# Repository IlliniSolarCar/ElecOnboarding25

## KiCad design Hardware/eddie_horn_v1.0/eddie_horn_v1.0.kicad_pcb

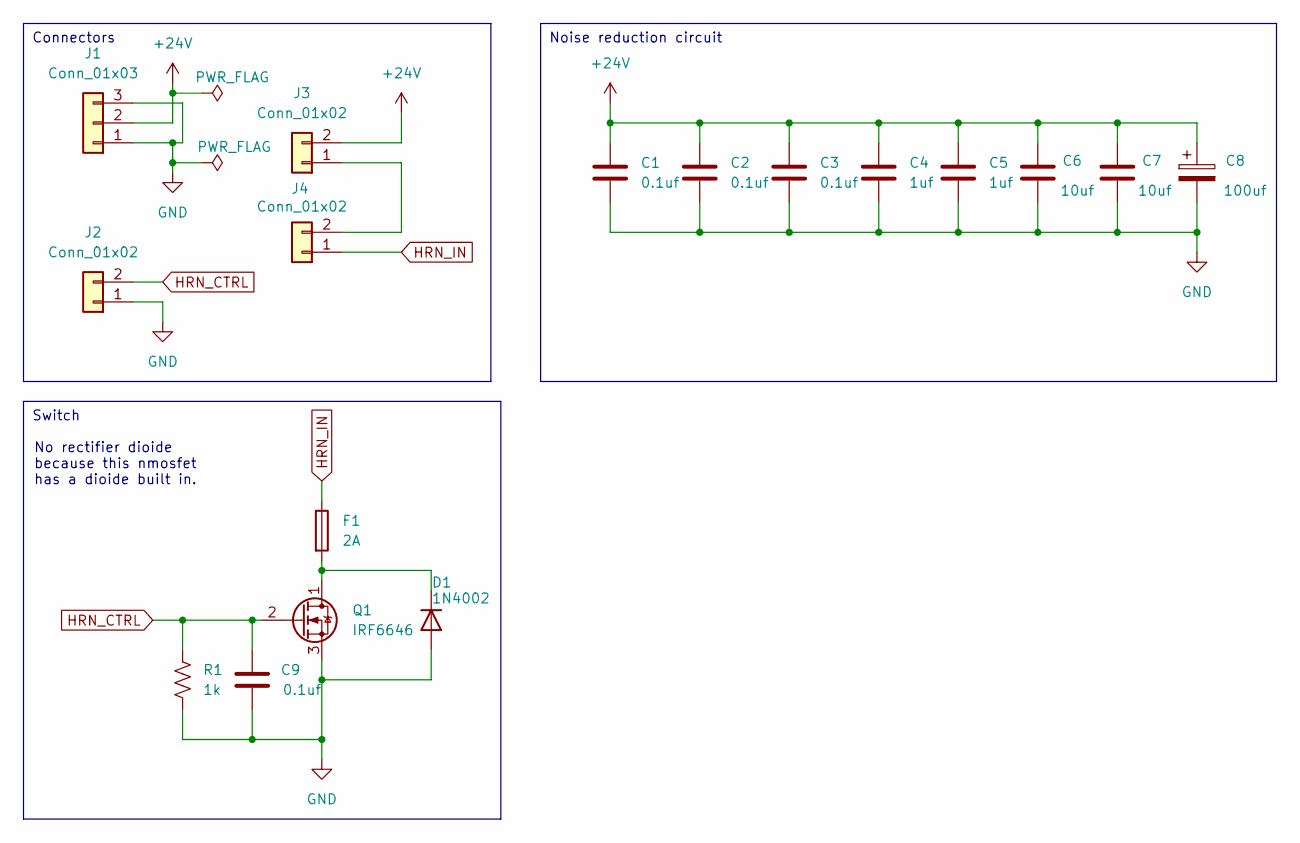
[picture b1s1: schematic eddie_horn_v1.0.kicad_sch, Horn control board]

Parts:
C1, C2, C3, C9: 0.1uf; C_0603_1608Metric_Pad1.08x0.95mm_HandSolder
C4, C5: 1uf; C_0603_1608Metric_Pad1.08x0.95mm_HandSolder
C6, C7: 10uf; C_0603_1608Metric_Pad1.08x0.95mm_HandSolder
C8: 100uf; CP_Radial_D10.0mm_P5.00mm
D1: 1N4002; D_DO-41_SOD81_P10.16mm_Horizontal
F1: 2A; Fuse_0603_1608Metric_Pad1.05x0.95mm_HandSolder
J1: Conn_01x03; Molex_Micro-Fit_3.0_43650-0300_1x03_P3.00mm_Horizontal
J2, J3, J4: Conn_01x02; Molex_Micro-Fit_3.0_43650-0200_1x02_P3.00mm_Horizontal
Q1: IRF6646; DirectFET_MN
R1: 1k; R_0603_1608Metric_Pad0.98x0.95mm_HandSolder

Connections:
+24V: C1.1, C2.1, C3.1, C4.1, C5.1, C6.1, C7.1, C8.1, J1.2, J3.2; also elsewhere on the board
GND: C1.2, C2.2, C3.2, C4.2, C5.2, C6.2, C7.2, C8.2, C9.2, D1.2 (A), J1.1, J1.3, J2.1, Q1.3 (S), R1.2
HRN_CTRL: C9.1, J2.2, Q1.2 (G), R1.1
HRN_IN: F1.1, J4.1; also elsewhere on the board
unnamed: J3.1, J4.2
unnamed: D1.1 (K), F1.2, Q1.1 (D)

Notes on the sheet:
Connectors
Noise reduction circuit
Switch
No rectifier dioide because this nmosfet has a dioide built in.

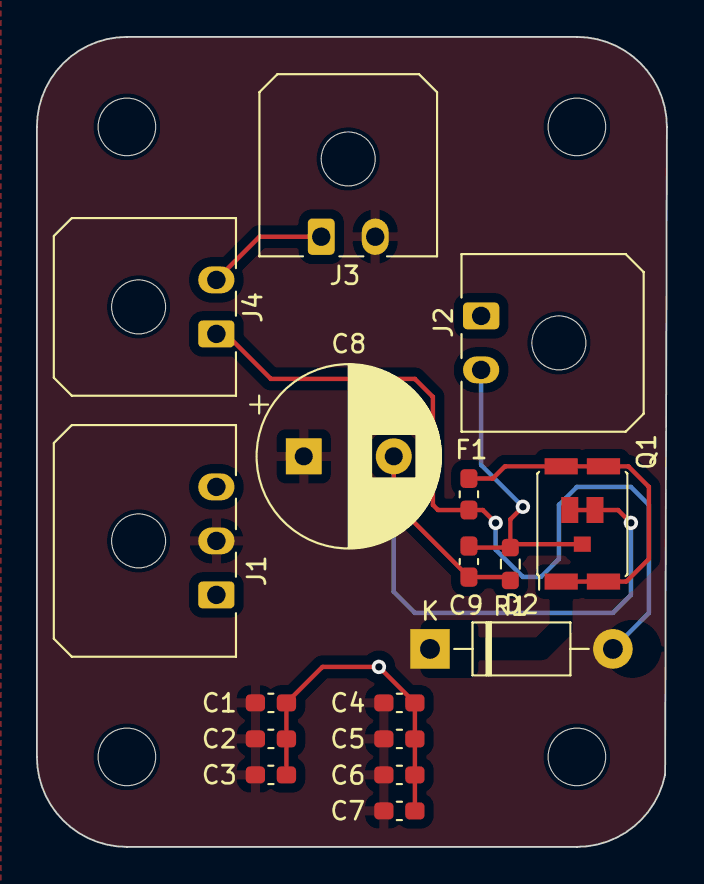
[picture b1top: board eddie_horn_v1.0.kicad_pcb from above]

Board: 2 copper layers, 35.0 x 45.0 mm, 17 parts (0 on the bottom side), 6 nets.

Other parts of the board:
D2: 1N4002; D_DO-41_SOD81_P10.16mm_Horizontal

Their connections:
+24V: D2.1 (K); also elsewhere on the board
HRN_IN: D2.2 (A); also elsewhere on the board

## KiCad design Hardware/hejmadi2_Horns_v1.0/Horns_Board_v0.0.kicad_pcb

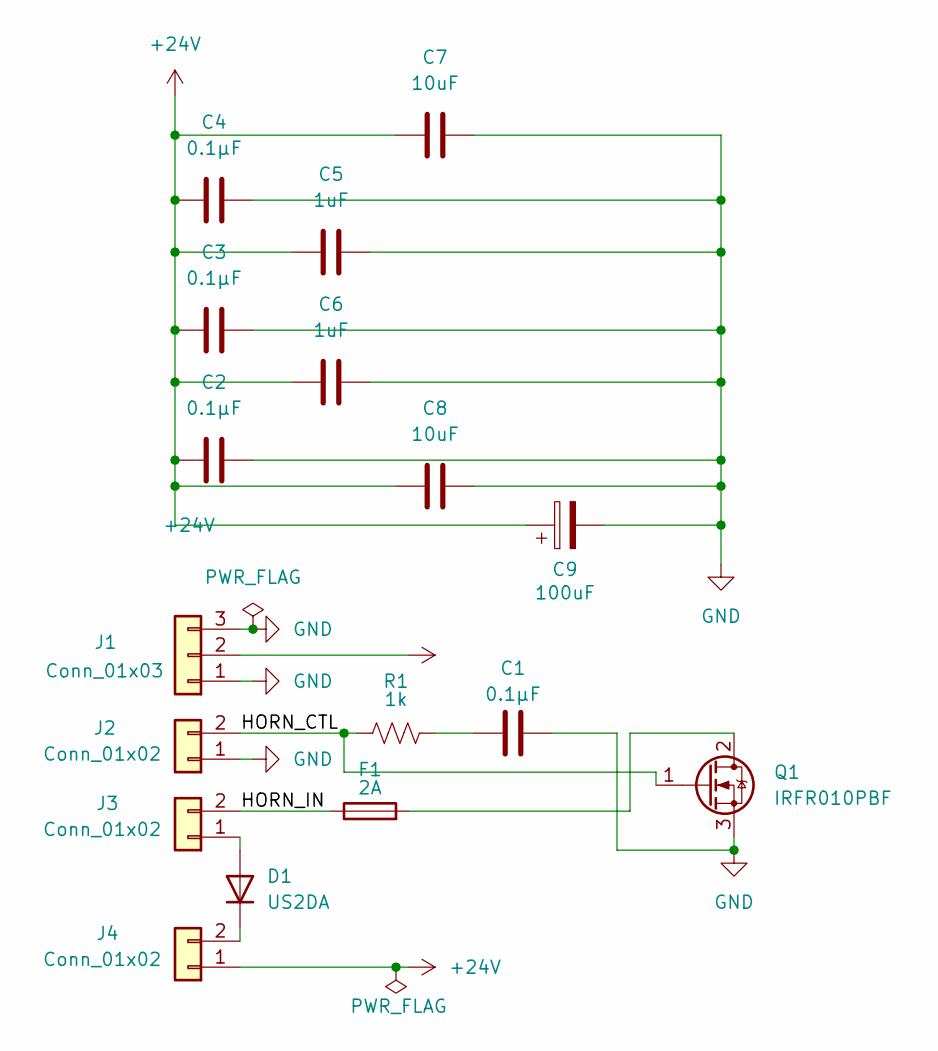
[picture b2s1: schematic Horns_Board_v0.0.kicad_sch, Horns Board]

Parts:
C1, C2, C3, C4: 0.1µF; C_0603_1608Metric_Pad1.08x0.95mm_HandSolder
C5, C6: 1uF; C_0603_1608Metric_Pad1.08x0.95mm_HandSolder
C7, C8: 10uF; C_0603_1608Metric_Pad1.08x0.95mm_HandSolder
C9: 100uF; C_0603_1608Metric_Pad1.08x0.95mm_HandSolder
D1: US2DA; D_SMA
F1: 2A; Fuse_0603_1608Metric_Pad1.05x0.95mm_HandSolder
J1: Conn_01x03; Molex_Micro-Fit_3.0_43650-0300_1x03_P3.00mm_Horizontal
J2, J3, J4: Conn_01x02; Molex_Micro-Fit_3.0_43650-0200_1x02_P3.00mm_Horizontal
Q1: IRFR010PBF; Fairchild_DualPower33-6_3x3mm
R1: 1k; R_0603_1608Metric_Pad0.98x0.95mm_HandSolder

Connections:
+24V: C2.1, C3.1, C4.1, C5.1, C6.1, C7.1, C8.1, C9.1, J1.2, J4.1
/HORN_CTL: J2.2, Q1.1 (G), R1.1
/HORN_IN: F1.1, J3.2
GND: C1.2, C2.2, C3.2, C4.2, C5.2, C6.2, C7.2, C8.2, C9.2, J1.1, J1.3, J2.1, Q1.3 (S)
unnamed: C1.1, R1.2
unnamed: D1.2 (A), J3.1
unnamed: D1.1 (K), J4.2
unnamed: F1.2, Q1.2 (D)

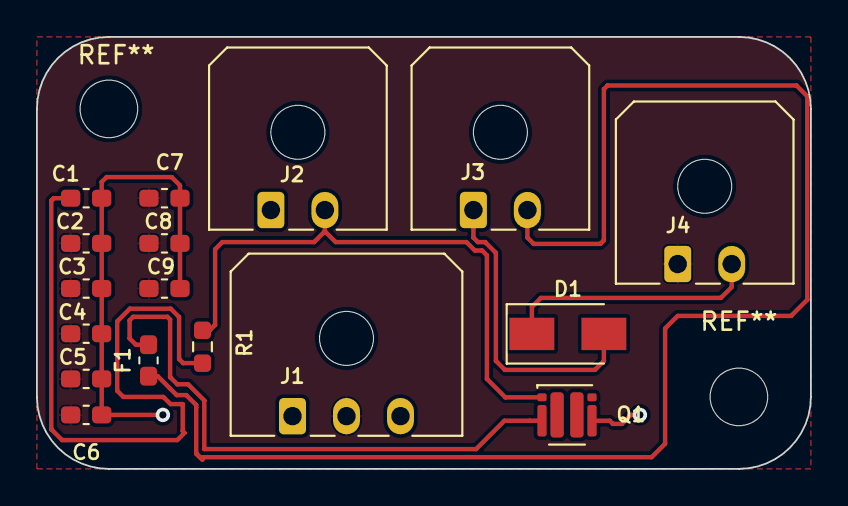
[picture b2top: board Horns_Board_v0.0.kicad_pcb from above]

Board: 2 copper layers, 43.0 x 24.0 mm, 17 parts (0 on the bottom side), 8 nets.

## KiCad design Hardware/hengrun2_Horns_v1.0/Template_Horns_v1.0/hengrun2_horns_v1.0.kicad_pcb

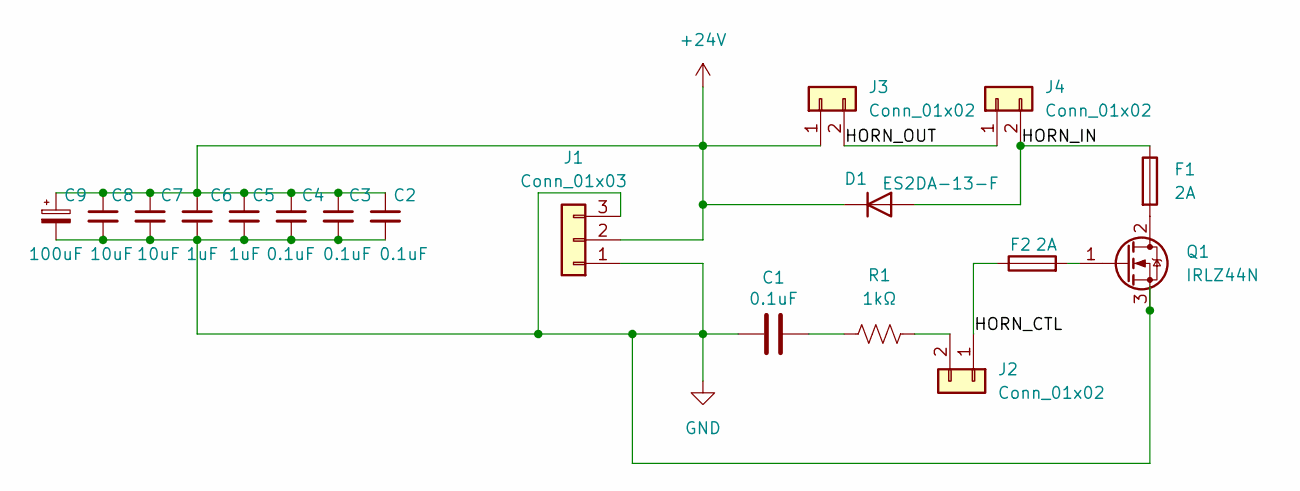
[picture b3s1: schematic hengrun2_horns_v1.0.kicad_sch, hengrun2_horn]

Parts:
C1, C2, C3, C4: 0.1uF; C_0603_1608Metric
C5, C6: 1uF; C_0603_1608Metric
C7, C8: 10uF; C_0603_1608Metric
C9: 100uF; CP_Radial_D5.0mm_P2.50mm
D1: ES2DA-13-F; D_SMA
F1, F2: 2A; Fuse_1206_3216Metric
J1: Conn_01x03; Molex_KK-254_AE-6410-03A_1x03_P2.54mm_Vertical
J2, J3, J4: Conn_01x02; Molex_KK-254_AE-6410-02A_1x02_P2.54mm_Vertical
Q1: IRLZ44N; TO-220-3_Vertical
R1: 1kΩ; R_0603_1608Metric_Pad0.98x0.95mm_HandSolder

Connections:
+24V: C2.1, C3.1, C4.1, C5.1, C6.1, C7.1, C8.1, C9.1, D1.1 (K), J1.2, J3.1
/HORN_CTL: F2.1, J2.1
/HORN_IN: D1.2 (A), F1.1, J4.2
/HORN_OUT: J3.2, J4.1
GND: C1.1, C2.2, C3.2, C4.2, C5.2, C6.2, C7.2, C8.2, C9.2, J1.1, J1.3, Q1.3 (S)
unnamed: C1.2, R1.1
unnamed: J2.2, R1.2
unnamed: F1.2, Q1.2 (D)
unnamed: F2.2, Q1.1 (G)

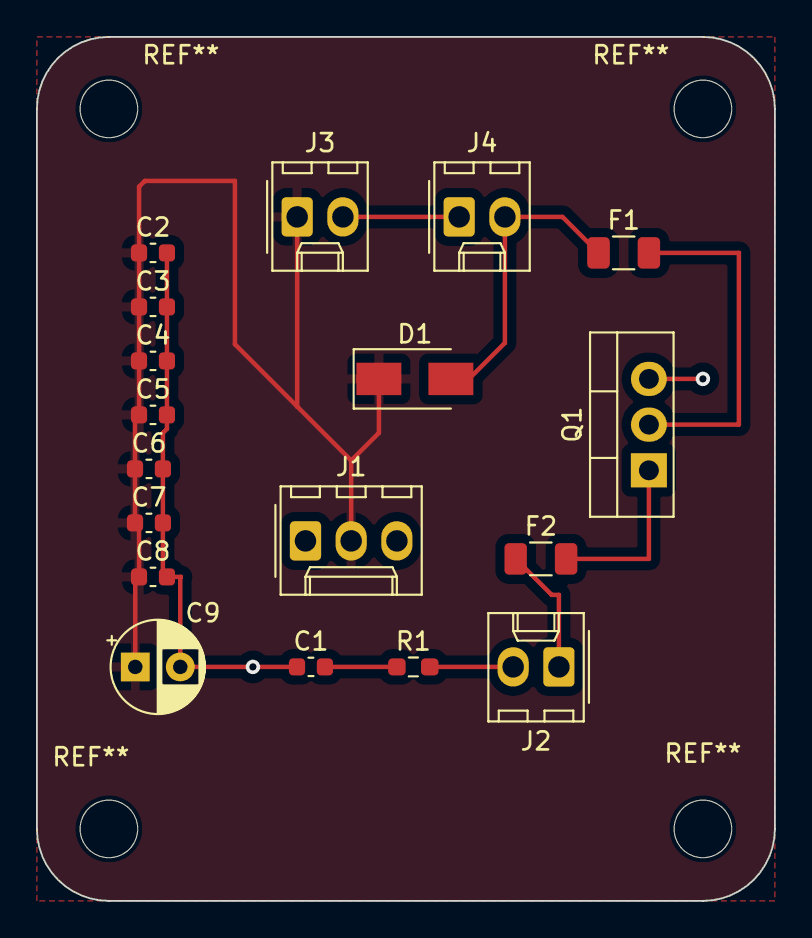
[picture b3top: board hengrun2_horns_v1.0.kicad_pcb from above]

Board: 2 copper layers, 41.0 x 48.0 mm, 18 parts (0 on the bottom side), 9 nets.

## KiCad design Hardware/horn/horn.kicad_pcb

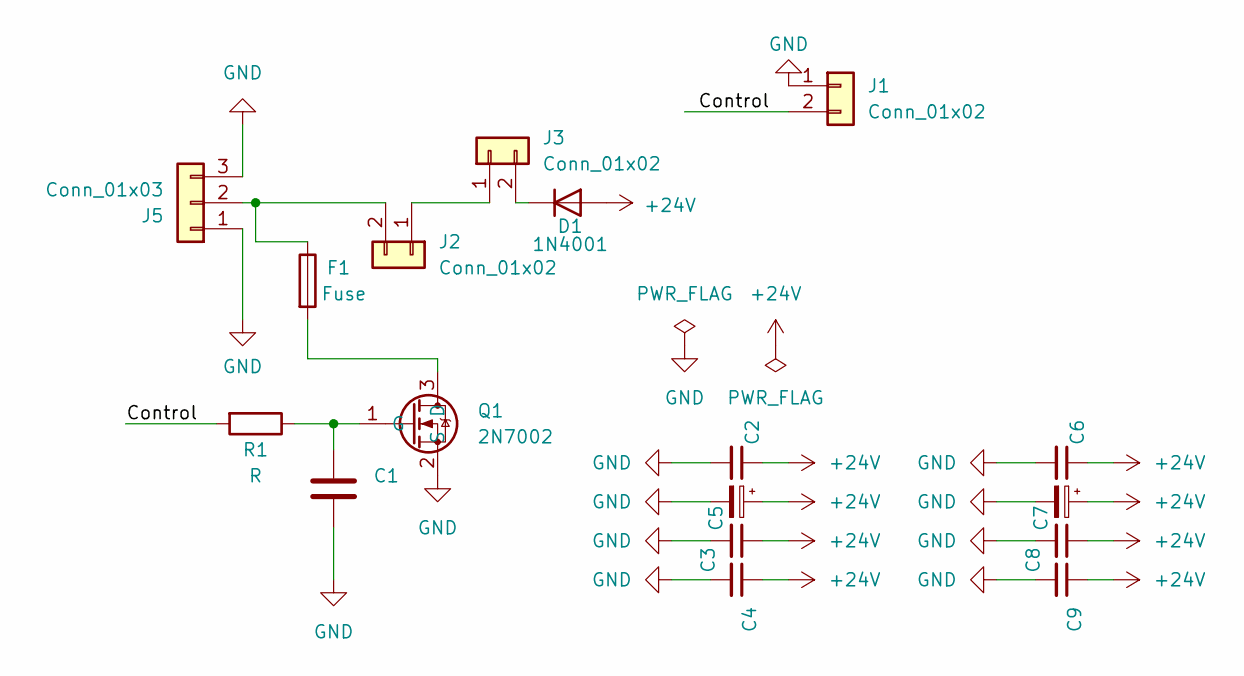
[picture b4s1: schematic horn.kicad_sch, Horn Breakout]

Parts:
C1: C; C_0201_0603Metric
C2, C3, C4, C6, C8, C9: C_Small; C_0201_0603Metric
C5, C7: C_Polarized_Small; CP_Elec_3x5.3
D1: 1N4001; D_DO-41_SOD81_P10.16mm_Horizontal
F1: Fuse; Fuse_0402_1005Metric
J1, J2, J3: Conn_01x02; Molex_KK-254_AE-6410-02A_1x02_P2.54mm_Vertical
J5: Conn_01x03; Molex_KK-254_AE-6410-03A_1x03_P2.54mm_Vertical
Q1: 2N7002; SOT-23
R1: R; R_0603_1608Metric_Pad0.98x0.95mm_HandSolder

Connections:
+24V: C2.1, C3.1, C4.1, C5.1, C6.1, C7.1, C8.1, C9.1, D1.2 (A)
/Control: J1.2, R1.2
GND: C1.2, C2.2, C3.2, C4.2, C5.2, C6.2, C7.2, C8.2, C9.2, J1.1, J5.1, J5.3, Q1.2 (S)
unnamed: D1.1 (K), J3.2
unnamed: J2.1, J3.1
unnamed: F1.1, J2.2, J5.2
unnamed: F1.2, Q1.3 (D)
unnamed: C1.1, Q1.1 (G), R1.1

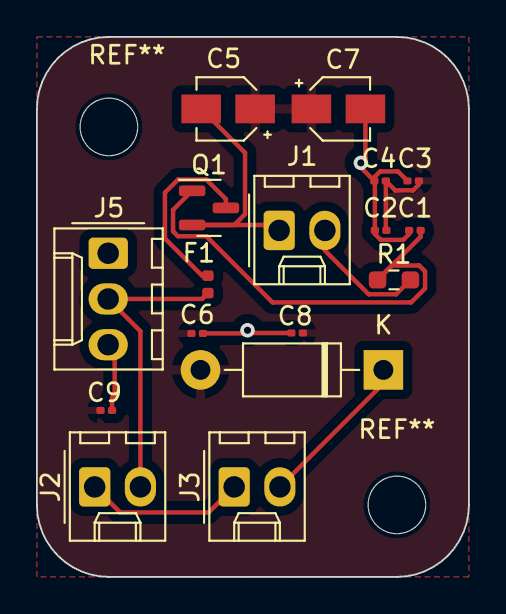
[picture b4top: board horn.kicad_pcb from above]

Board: 2 copper layers, 24.0 x 30.0 mm, 17 parts (0 on the bottom side), 8 nets.

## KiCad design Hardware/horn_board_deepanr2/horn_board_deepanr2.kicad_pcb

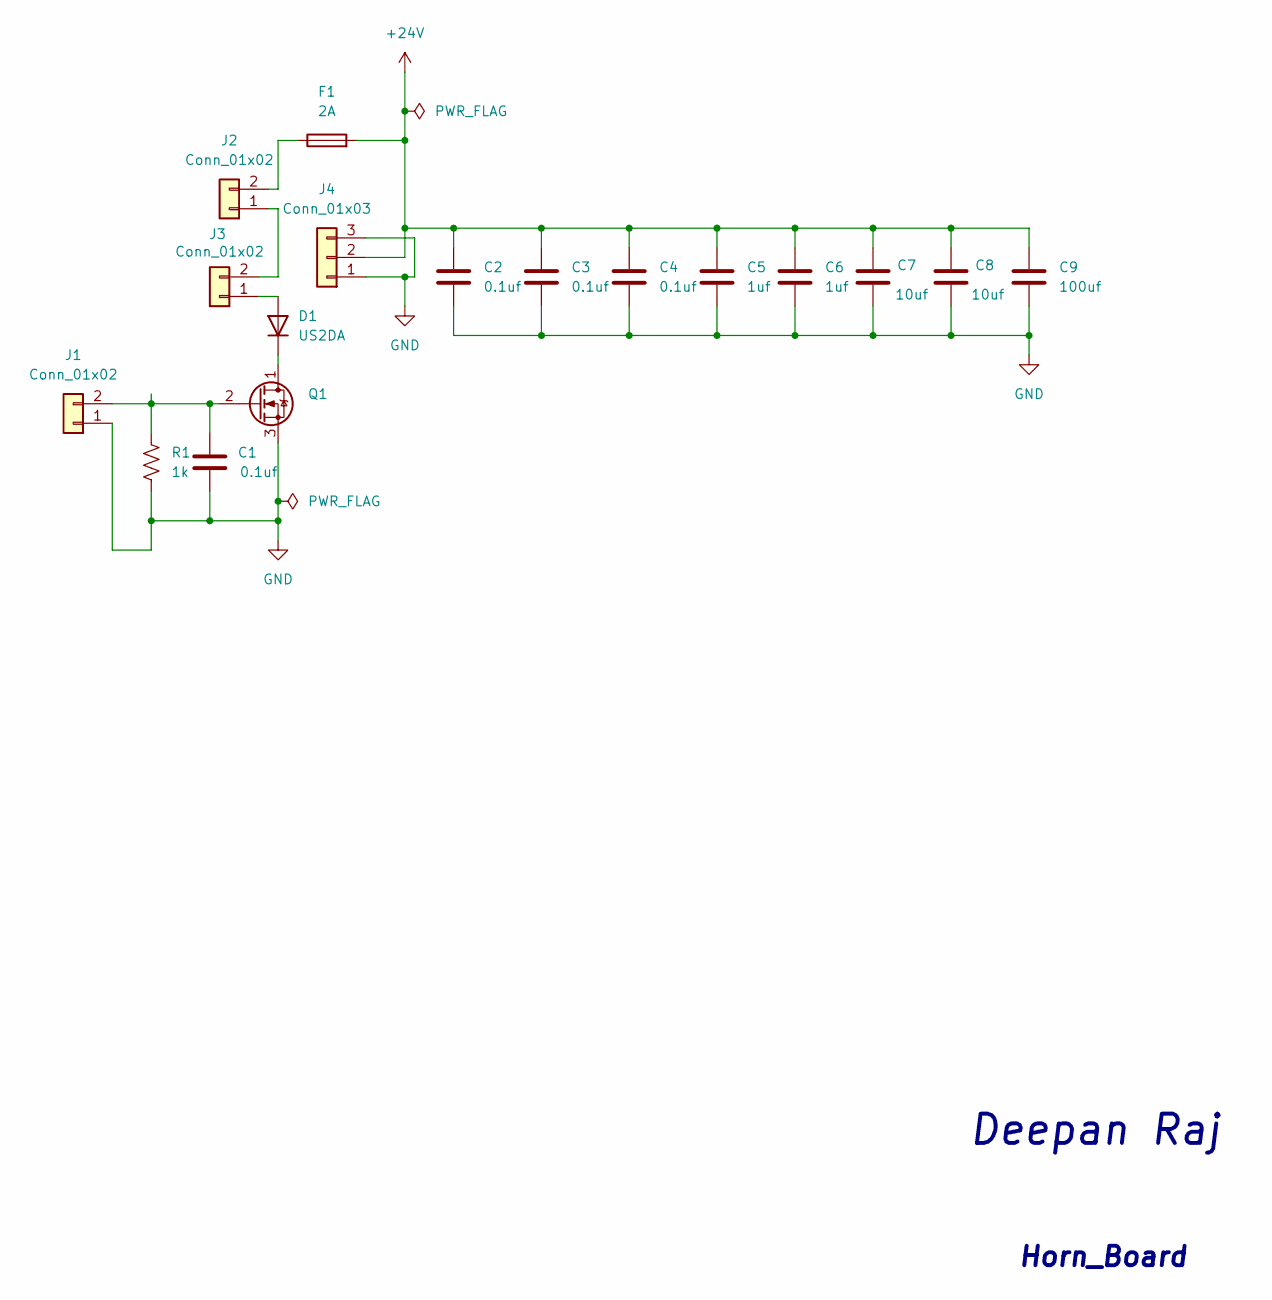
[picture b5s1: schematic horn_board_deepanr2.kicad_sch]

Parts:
C1, C2, C3, C4: 0.1uf; C_0603_1608Metric_Pad1.08x0.95mm_HandSolder
C5, C6: 1uf; C_0603_1608Metric_Pad1.08x0.95mm_HandSolder
C7, C8: 10uf; C_0603_1608Metric_Pad1.08x0.95mm_HandSolder
C9: 100uf
D1: US2DA; D_SMA
F1: 2A; Fuse_0603_1608Metric_Pad1.05x0.95mm_HandSolder
J1, J2, J3: Conn_01x02; Molex_KK-254_AE-6410-02A_1x02_P2.54mm_Vertical
J4: Conn_01x03; Molex_KK-254_AE-6410-03A_1x03_P2.54mm_Vertical
Q1: IRF6646; DirectFET_MN
R1: 1k; R_0603_1608Metric_Pad0.98x0.95mm_HandSolder

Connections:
+24V: C2.1, C3.1, C4.1, C5.1, C6.1, C7.1, C8.1, C9.1, F1.2, J4.2
GND: C1.2, C2.2, C3.2, C4.2, C5.2, C6.2, C7.2, C8.2, C9.2, J1.1, J4.1, J4.3, Q1.3 (S), R1.2
unnamed: D1.2 (A), J3.1
unnamed: D1.1 (K), Q1.1 (D)
unnamed: C1.1, J1.2, Q1.2 (G), R1.1
unnamed: J2.1, J3.2
unnamed: F1.1, J2.2

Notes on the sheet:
Horn_Board
Deepan Raj

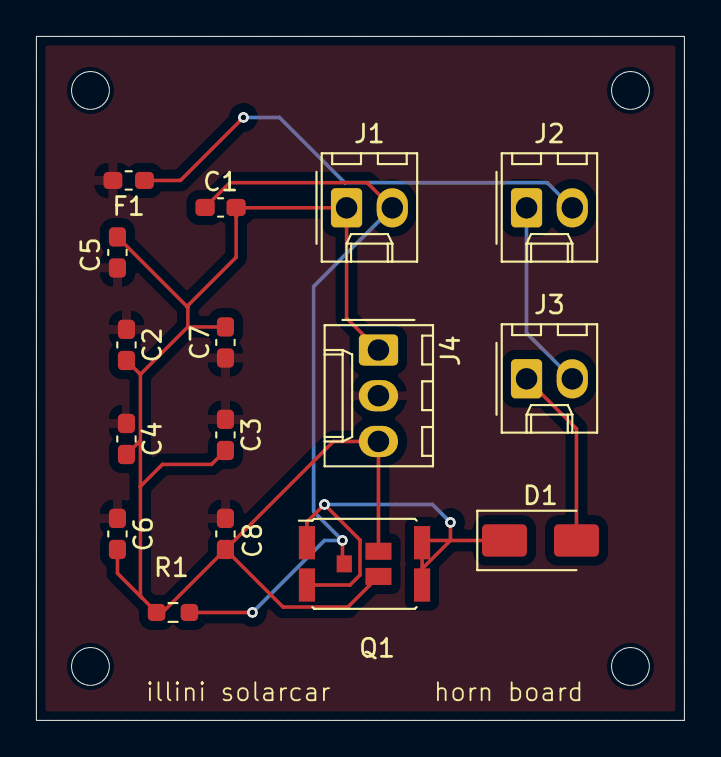
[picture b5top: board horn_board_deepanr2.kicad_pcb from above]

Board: 2 copper layers, 36.0 x 38.0 mm, 16 parts (0 on the bottom side), 7 nets.

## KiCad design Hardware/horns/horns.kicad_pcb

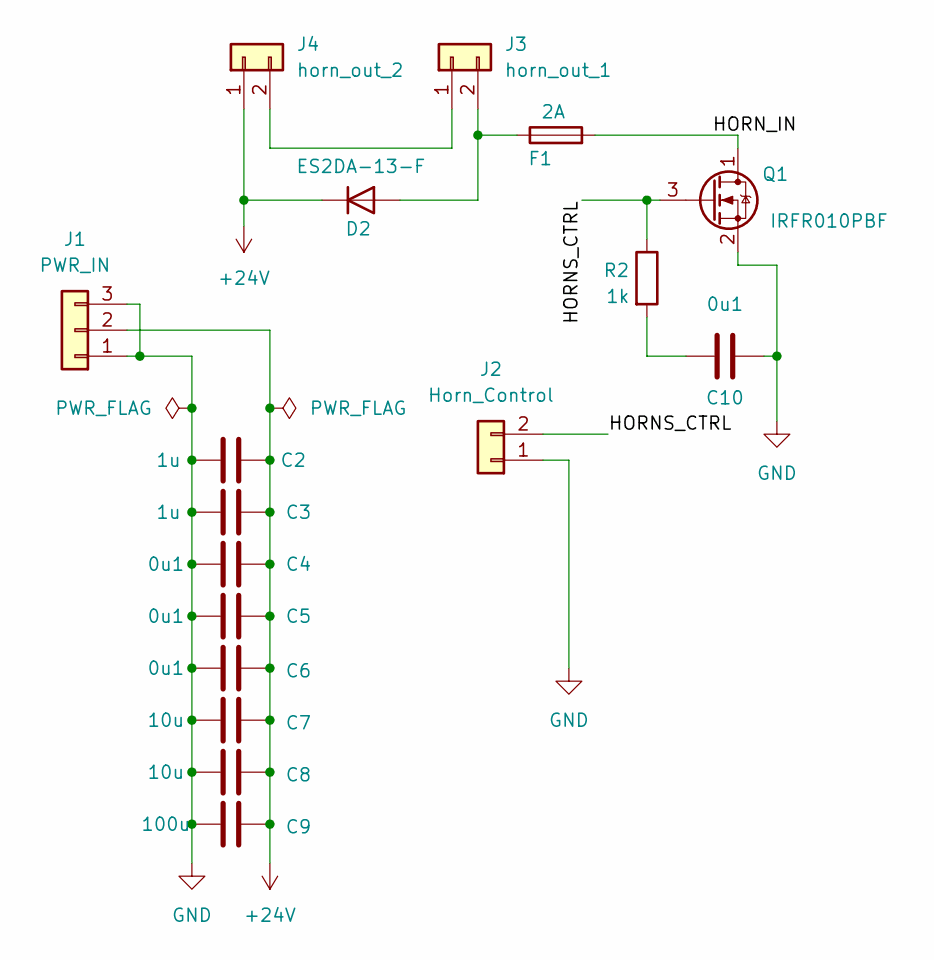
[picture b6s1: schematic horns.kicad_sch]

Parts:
C2, C3: 1u; C_0805_2012Metric
C4, C5, C6, C10: 0u1; C_0805_2012Metric
C7, C8: 10u; C_0805_2012Metric
C9: 100u; CP_Oval_L16.0mm_W8.0mm_P11.5mm
D2: ES2DA-13-F; D_SMA
F1: 2A; Fuse_Littelfuse_1206
J1: PWR_IN; Molex_KK-254_1x03_P2.54mm_Horizontal
J2: Horn_Control; Molex_KK-254_1x02_P2.54mm_Horizontal
J3: horn_out_1; Molex_KK-254_1x02_P2.54mm_Horizontal
J4: horn_out_2; Molex_KK-254_1x02_P2.54mm_Horizontal
Q1: IRFR010PBF; TO-252-2
R2: 1k; R_0603_1608Metric_Pad0.98x0.95mm_HandSolder

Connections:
+24V: C2.2, C3.2, C4.2, C5.2, C6.2, C7.2, C8.2, C9.2, D2.1 (K), J1.2, J4.1; also elsewhere on the board
/HORNS_CTRL: J2.2, Q1.3 (G), R2.1
/HORN_IN: F1.2, Q1.1 (D)
GND: C2.1, C3.1, C4.1, C5.1, C6.1, C7.1, C8.1, C9.1, C10.1, J1.1, J1.3, J2.1, Q1.2 (S); also elsewhere on the board
unnamed: C10.2, R2.2
unnamed: D2.2 (A), F1.1, J3.2
unnamed: J3.1, J4.2

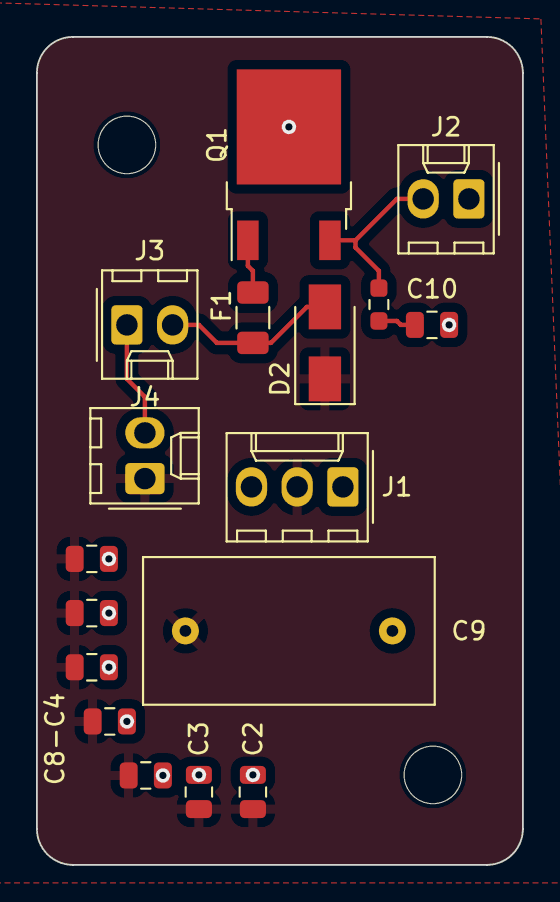
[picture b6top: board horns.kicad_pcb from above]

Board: 2 copper layers, 27.0 x 46.0 mm, 17 parts (0 on the bottom side), 7 nets.

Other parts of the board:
C8-C4: 10u; C_0805_2012Metric

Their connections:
+24V: C8-C4.2; also elsewhere on the board
GND: C8-C4.1; also elsewhere on the board

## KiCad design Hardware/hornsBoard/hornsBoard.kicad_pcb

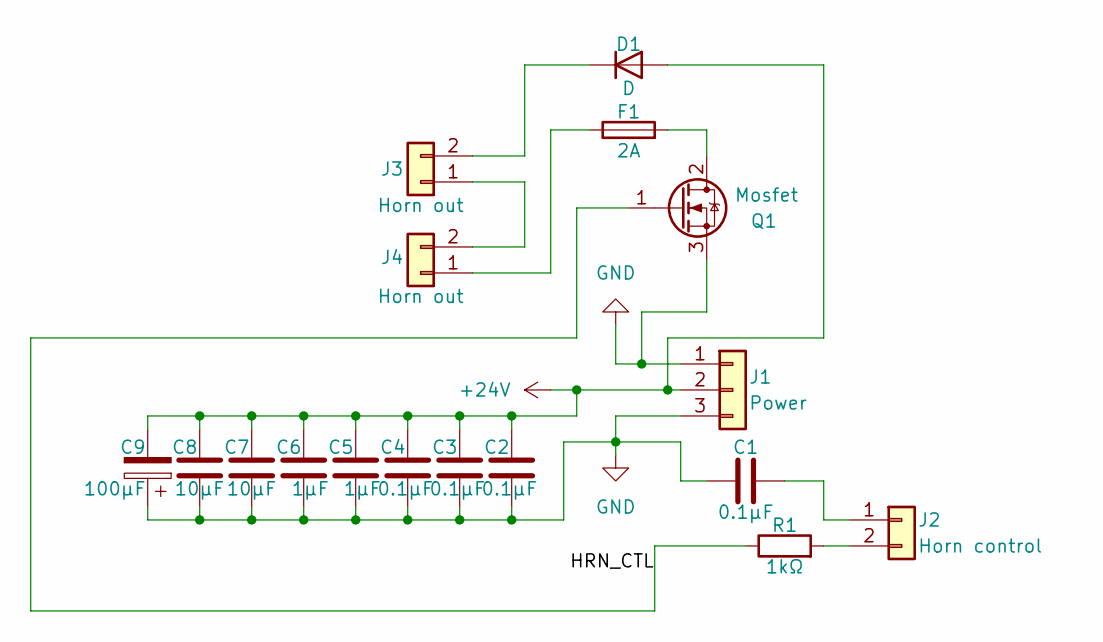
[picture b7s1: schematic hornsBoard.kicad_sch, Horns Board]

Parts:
C1, C2, C3, C4: 0.1µF; C_0603_1608Metric
C5, C6: 1µF; C_0805_2012Metric
C7, C8: 10µF; C_1206_3216Metric
C9: 100µF; C_1210_3225Metric
D1: D; D_SMA
F1: 2A; Fuse_1206_3216Metric
J1: Power; Molex_Micro-Fit_3.0_43650-0300_1x03_P3.00mm_Horizontal
J2: Horn control; Molex_Micro-Fit_3.0_43650-0200_1x02_P3.00mm_Horizontal
J3, J4: Horn out; Molex_Micro-Fit_3.0_43650-0200_1x02_P3.00mm_Horizontal
Q1: Mosfet; TO-252-2
R1: 1kΩ; R_0805_2012Metric

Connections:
+24V: C2.1, C3.1, C4.1, C5.1, C6.1, C7.1, C8.1, C9.2, D1.2 (A), J1.2
/HRN_CTL: Q1.1 (G), R1.1
GND: C1.1, C2.2, C3.2, C4.2, C5.2, C6.2, C7.2, C8.2, C9.1, J1.1, J1.3, Q1.3 (S)
unnamed: D1.1 (K), J3.2
unnamed: C1.2, J2.1
unnamed: J2.2, R1.2
unnamed: J3.1, J4.2
unnamed: F1.1, J4.1
unnamed: F1.2, Q1.2 (D)

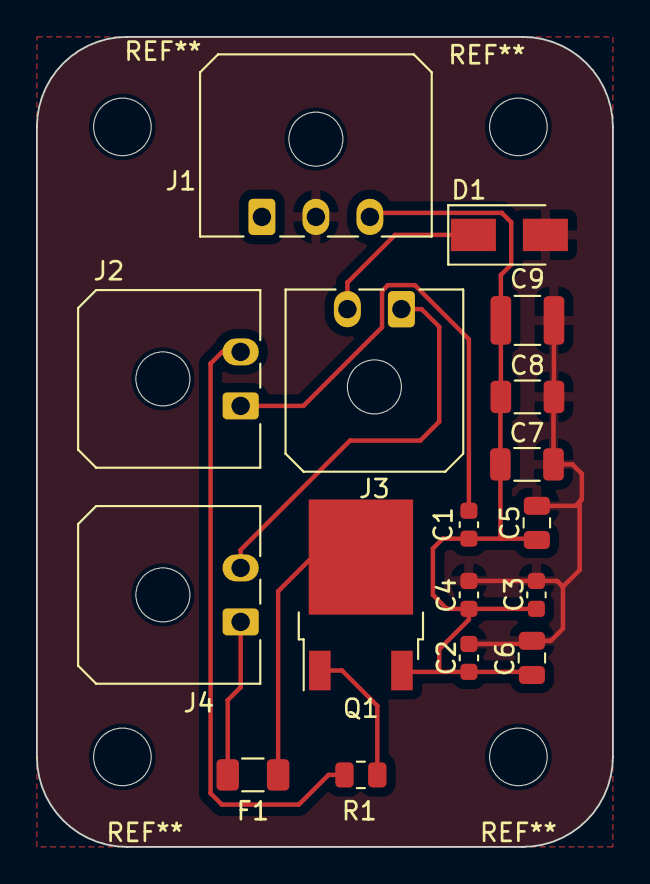
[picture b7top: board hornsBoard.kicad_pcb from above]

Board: 2 copper layers, 32.0 x 45.0 mm, 17 parts (0 on the bottom side), 9 nets.

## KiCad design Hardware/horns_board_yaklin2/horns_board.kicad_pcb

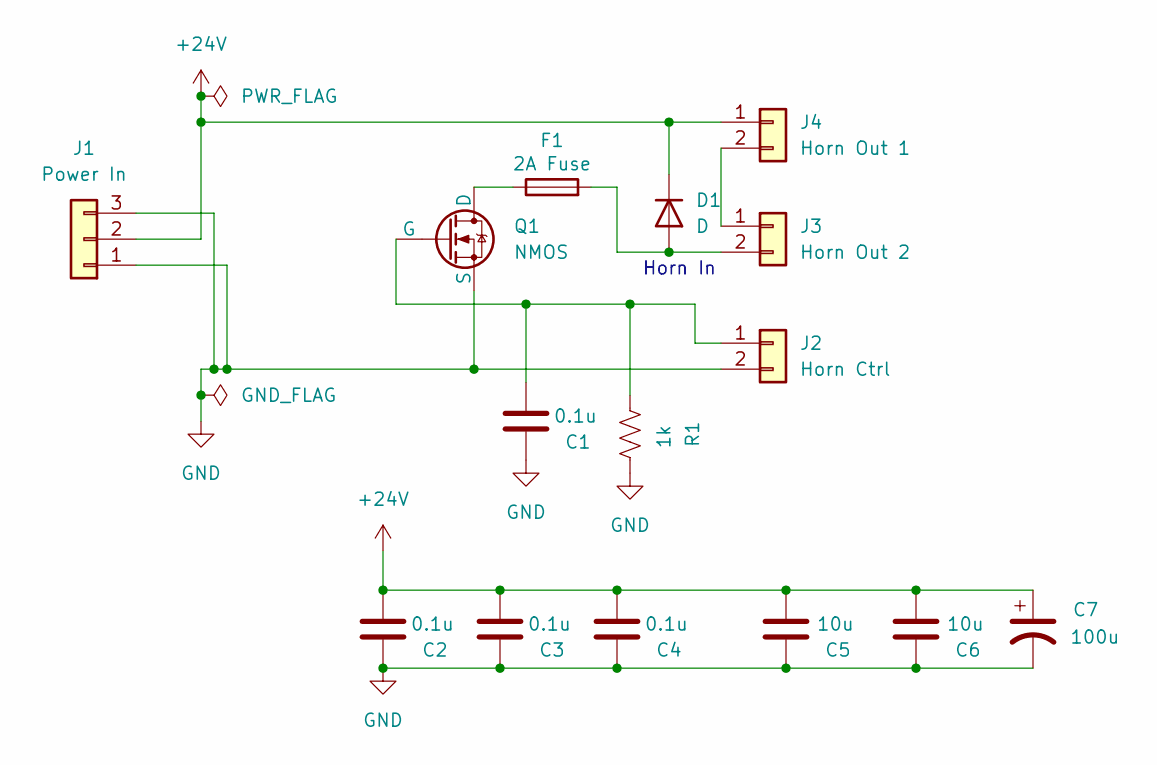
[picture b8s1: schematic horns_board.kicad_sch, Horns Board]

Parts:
C1, C2, C3, C4: 0.1u; C_0603_1608Metric_Pad1.08x0.95mm_HandSolder
C5, C6: 10u; C_0603_1608Metric_Pad1.08x0.95mm_HandSolder
C7: 100u; CP_Radial_Tantal_D6.0mm_P5.00mm
D1: D; D_0201_0603Metric_Pad0.64x0.40mm_HandSolder
F1: 2A Fuse; Fuse_0603_1608Metric_Pad1.05x0.95mm_HandSolder
J1: Power In; Molex_KK-254_AE-6410-03A_1x03_P2.54mm_Vertical
J2: Horn Ctrl; Molex_KK-254_AE-6410-02A_1x02_P2.54mm_Vertical
J3: Horn Out 2; Molex_KK-254_AE-6410-02A_1x02_P2.54mm_Vertical
J4: Horn Out 1; Molex_KK-254_AE-6410-02A_1x02_P2.54mm_Vertical
Q1: NMOS; TO-252-2
R1: 1k; R_0201_0603Metric_Pad0.64x0.40mm_HandSolder

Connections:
+24V: C2.2, C3.2, C4.2, C5.2, C6.2, C7.1, D1.1 (K), J1.2, J4.1
GND: C1.1, C2.1, C3.1, C4.1, C5.1, C6.1, C7.2, J1.1, J1.3, J2.2, Q1.3 (S), R1.1
unnamed: D1.2 (A), F1.2, J3.2
unnamed: C1.2, J2.1, Q1.2 (G), R1.2
unnamed: J3.1, J4.2
unnamed: F1.1, Q1.1 (D)

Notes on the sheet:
Horn In

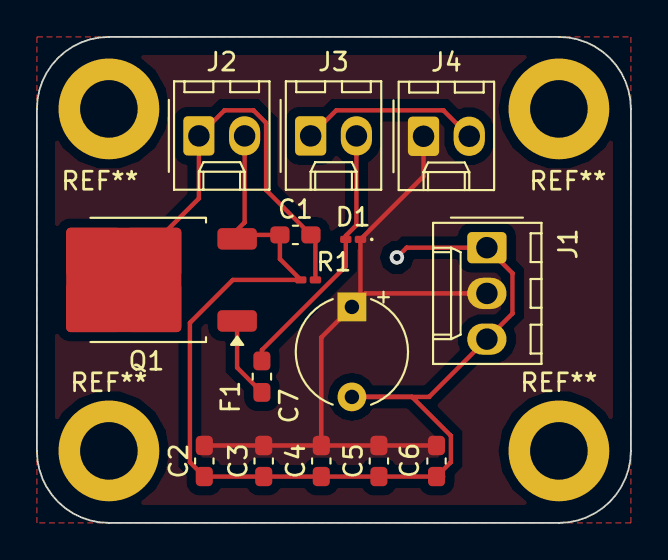
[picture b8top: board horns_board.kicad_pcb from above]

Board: 2 copper layers, 33.0 x 27.0 mm, 15 parts (0 on the bottom side), 6 nets.
